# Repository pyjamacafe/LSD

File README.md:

# LSD — Lattice iCE40HX1K-TQ144 USB Breadboard FPGA Core

> [!WARNING]
> **Work in Progress (WIP):** This hardware design is currently a work in progress and has not yet been fabricated or electrically validated on physical silicon. Review the schematic, BOM, and Gerbers carefully before ordering PCBs.

**LSD** (*"Warning: Highly Addictive!"*) is a minimal, breadboardable 2-layer **Lattice iCE40HX1K-TQ144** (1,280 LUTs) FPGA core board designed in **KiCad 10**. It is programmable directly over **USB Micro-B** with **no FTDI bridge chip** by running an open-source RTL USB DFU bootloader (`no2bootloader` / `no2usb`) directly inside the FPGA fabric.

| Top View | Bottom View (Pinout & Logo) |
| :---: | :---: |
|  |  |

---

## Hardware Specifications

* **FPGA:** Lattice `iCE40HX1K-TQ144` (1,280 4-LUTs, 64 kbit EBR, 1× `SB_PLL40_CORE`, 144-pin 0.5 mm TQFP)
* **Form Factor:** `31.2 mm × 64.0 mm` 2-layer FR-4 PCB (1.6 mm) with **`1.5 mm` rounded corners**, filled `B.Cu` ground plane, 45°-mitered routing, and crisp `0.65 mm` non-overlapping top silkscreen references (`0` silk-over-pad)
* **Breadboard Headers:** Two 1×20 2.54 mm through-hole rows (`J3` left, `J4` right) spaced **`27.94 mm` (1.100″ / 11 × 2.54 mm)** apart center-to-center — **36× 3.3V GPIOs**, `+3V3` (top-left), `+5V` VBUS (top-right), and `GND` (bottom-left & bottom-right). Headers are unpopulated by default for user soldering.
* **FTDI-less USB Micro-B (`no2bootloader` ready):** Top-edge horizontal `Molex 47346-0001` (`J1`) → `USBLC6-2SC6` ESD protection (`U5`) → `27 Ω` 1% series damping resistors (`R1`, `R2`) + software-controlled `1.5 kΩ` `D+` pull-up (`R3`, on connector side of `R1`) wired directly to Bank 0 pins `129` (`USB_DN`), `128` (`USB_DP`), and `122` (`USB_PU`).
* **Clock:** `16 MHz` 3.3V CMOS oscillator (`Y1`, Abracon ASE 3.2×2.5 mm) wired to `GBIN6` (Pin `21`), multiplied to an exact `48.000 MHz` via `SB_PLL40_PAD` / `SB_PLL40_CORE` (`DIVR=0`, `DIVF=47`, `DIVQ=4`, `FILTER_RANGE=1`) for Full-Speed USB.
* **SPI Flash:** `W25Q16JVSS` (16 Mbit / 2 MB SOIC-8, `U2`) wired in Master SPI multiboot mode (`Pin 67 SDO → Flash DO`, `Pin 68 SDI → Flash DI`, `Pin 70 SCK`, `Pin 71 SS`) with `10 kΩ` pull-ups on `FLASH_CS_N`, `CRESET_B`, `CDONE`, `~WP`, and `~HOLD`.
* **Push Buttons (Omron `B3U-1000P`):**
  * **`RST` (`SW1`):** Pulls `CRESET_B` (Pin `66`) low to reset and reboot the FPGA from SPI Flash.
  * **`PROG` (`SW2`):** Active-low input on Pin `121` (`PROG_BTN_N`, `10 kΩ` pull-up `R10`). Hold **`PROG`** and tap **`RST`** to keep the FPGA in USB DFU bootloader mode.
* **Power Supply (Sequenced per Lattice `FPGA-TN-02006`):** Independent low-noise LDOs from USB 5V: `AP2112K-1.2` (`U4`, 1.2V Core + RC-filtered `VCCPLL` with isolated local `GNDPLL` return on Pin `35`/`C14`/`C13` — never tied to the main `GND` plane) ramps first, followed by `AP2112K-3.3` (`U3`, 3.3V I/O & Flash, `EN` delayed ~8–36 ms via `R11 = 10 kΩ` / `C19 = 10 µF`), and `1N4148W` drop diode (`D1`) for `VPP_2V5` — guaranteeing `+1V2`/`VCCPLL` (`≥ 0.5 V`) → `+3V3` (`SPI_VCC`) → `VPP_2V5`.
* **One-Time SPI Bootstrap Header (`J2`):** Unpopulated 2×4 2.54 mm header at the bottom edge (`3V3`, `GND`, `CS`, `SCK`, `DI`, `DO`, `RST`, `DN`) for flashing the bootloader once onto a blank SPI Flash.

---

## Verification (KiCad `10.0.3` CLI — Rev `2.5`)

* **Schematic ERC (`kicad-cli sch erc`):** `0` errors, `0` warnings
* **2-Layer PCB DRC (`kicad-cli pcb drc`, saved filled `B.Cu` `GND` zone):** `0` errors, `0` unconnected items, `0` `silk_over_copper` warnings
* **Gerbers (`--check-zones`):** Verified filled `B.Cu` `GND` pour (`G36`), `1.5 mm` rounded `Edge.Cuts`, and 43/43 1:1 BOM/CPL parity

---

## Programming Guide (Direct USB Bootloader)

Because the `iCE40HX1K` has **1,280 LUTs** (no SPRAM), it supports compact pure-Verilog Full-Speed USB bootloaders — such as **`TinyFPGA-Bootloader`** (~950–1,050 LUTs, works out of the box on `HX1K` with `tinyprog`) or a lightweight pure-Verilog **`no2usb`** DFU FSM (note: the full RISC-V `no2bootloader` targets `iCE40UP5K` and exceeds 1,280 LUTs). Both use the exact same hardware (`16 MHz → 48 MHz` PLL, `27 Ω` series `D+`/`D-`, `1.5 kΩ` software `USB_PU`, `W25Q16JVSS` SPI Flash).

### Prerequisites
Install the open-source IceStorm FPGA toolchain + `dfu-util` (e.g., via Homebrew on macOS or [OSS CAD Suite](https://github.com/YosysHQ/oss-cad-suite-build/releases)):
```bash
brew install yosys nextpnr-ice40 icestorm dfu-util
```

### Stage 1: One-Time Bootloader Bring-Up (via `J2`)
A blank `W25Q16JVSS` flash has no bitstream yet, so flash `no2bootloader` **once**:

1. **Build `no2bootloader` for `hx1k` (`tq144`)** using the pinout in [pins.pcf](pins.pcf):
   * `CLK_16M` → Pin `21` (`GBIN6`; 16 MHz → 48.000 MHz exact via `SB_PLL40_PAD`/`SB_PLL40_CORE` with `DIVR=0`, `DIVF=47`, `DIVQ=4`, `FILTER_RANGE=1`)
   * `USB_DP` → Pin `128`, `USB_DN` → Pin `129` (`27 Ω` series), `USB_PU` → Pin `122` (`1.5 kΩ` software pull-up)
   * `PROG_BTN_N` → Pin `121` (active-low, `10 kΩ` pull-up)
   * `FLASH_DO` → `67`, `FLASH_DI` → `68`, `FLASH_SCK` → `70`, `FLASH_CS_N` → `71`
2. **Pack the multiboot image** with `icemulti` (Slot 0 = bootloader, Slot 1 = user bitstream):
   ```bash
   icemulti -v -p0 -a16 -o flash_init.bin boot.bin
   ```
3. **Wire a 3.3V SPI programmer** (Raspberry Pi, RP2040/Pico, FT232H, or 3.3V CH341A) to `J2` (`3V3`, `GND`, `CS`, `SCK`, `DI`, `DO`) and hold **`RST` (`CRESET_B`) LOW** to tri-state the FPGA SPI pins.
4. **Flash `flash_init.bin` to `W25Q16JVSS` at offset `0x000000`:**
   ```bash
   flashrom -p <your_3v3_programmer> -w flash_init.bin
   ```
5. **Release `RST` and disconnect `J2`.** All future programming happens over USB Micro-B.

### Stage 2: Everyday Programming Over USB Micro-B
1. **Synthesize and pack your Verilog design:**
   ```bash
   yosys -p "synth_ice40 -top top -json build.json" top.v
   nextpnr-ice40 --hx1k --package tq144 --pcf pins.pcf --json build.json --asc build.asc
   icepack build.asc build.bin
   ```
2. **Enter USB DFU mode:** Plug in USB Micro-B, **hold `PROG`**, **tap `RST`**, then release `PROG`. Verify with `dfu-util -l`.
3. **Flash over USB:**
   ```bash
   dfu-util -a 0 -D build.bin -R
   ```
   The `-R` flag triggers `SB_WARMBOOT` to immediately reboot into your design. Tap **`RST`** anytime to reboot.

---

## Interactive 3D Viewer & Project Files

To inspect the photorealistic PBR 3D board in your browser:
```bash
python3 -m http.server 8000
# Open http://localhost:8000/viewer.html
```

| Path | Description |
| :--- | :--- |
| `ice40hx1k_usb_core.kicad_pro` | KiCad 10 project & 2-layer design rules |
| `ice40hx1k_usb_core.kicad_sch` | Complete schematic (`0` ERC violations) |
| `ice40hx1k_usb_core.kicad_pcb` | Routed `31.2 × 64.0 mm` 2-layer PCB (`0` DRC errors, `0` unconnected) |
| `pins.pcf` | IceStorm / `nextpnr-ice40` pin constraint file matching back silkscreen |
| `fab/gerbers/` | Fabrication-ready 2-layer Gerber X2 + Excellon `.drl` + drill map |
| `fab/bom.csv` | Bill of Materials |
| `fab/lioncircuits/` | LionCircuits-formatted Gerber `.zip`, BOM `.xlsx`/`.csv`, and CPL `.xlsx`/`.csv` |
| `renders/ice40hx1k_usb_core.glb` | Full-detail PBR 3D model (WebGL / Three.js / `<model-viewer>`) |
| `renders/ice40hx1k_usb_core.step` | Mechanical CAD 3D model (Fusion 360 / FreeCAD / SolidWorks) |
| `renders/schematic.pdf` | Printable schematic PDF |
| `renders/logo.{svg,png,jpg}` | LSD square stamp-heart logo assets |
| `viewer.html` | Interactive `<model-viewer>` 3D PCB viewer |

---

## License

Released under the [MIT License](LICENSE).

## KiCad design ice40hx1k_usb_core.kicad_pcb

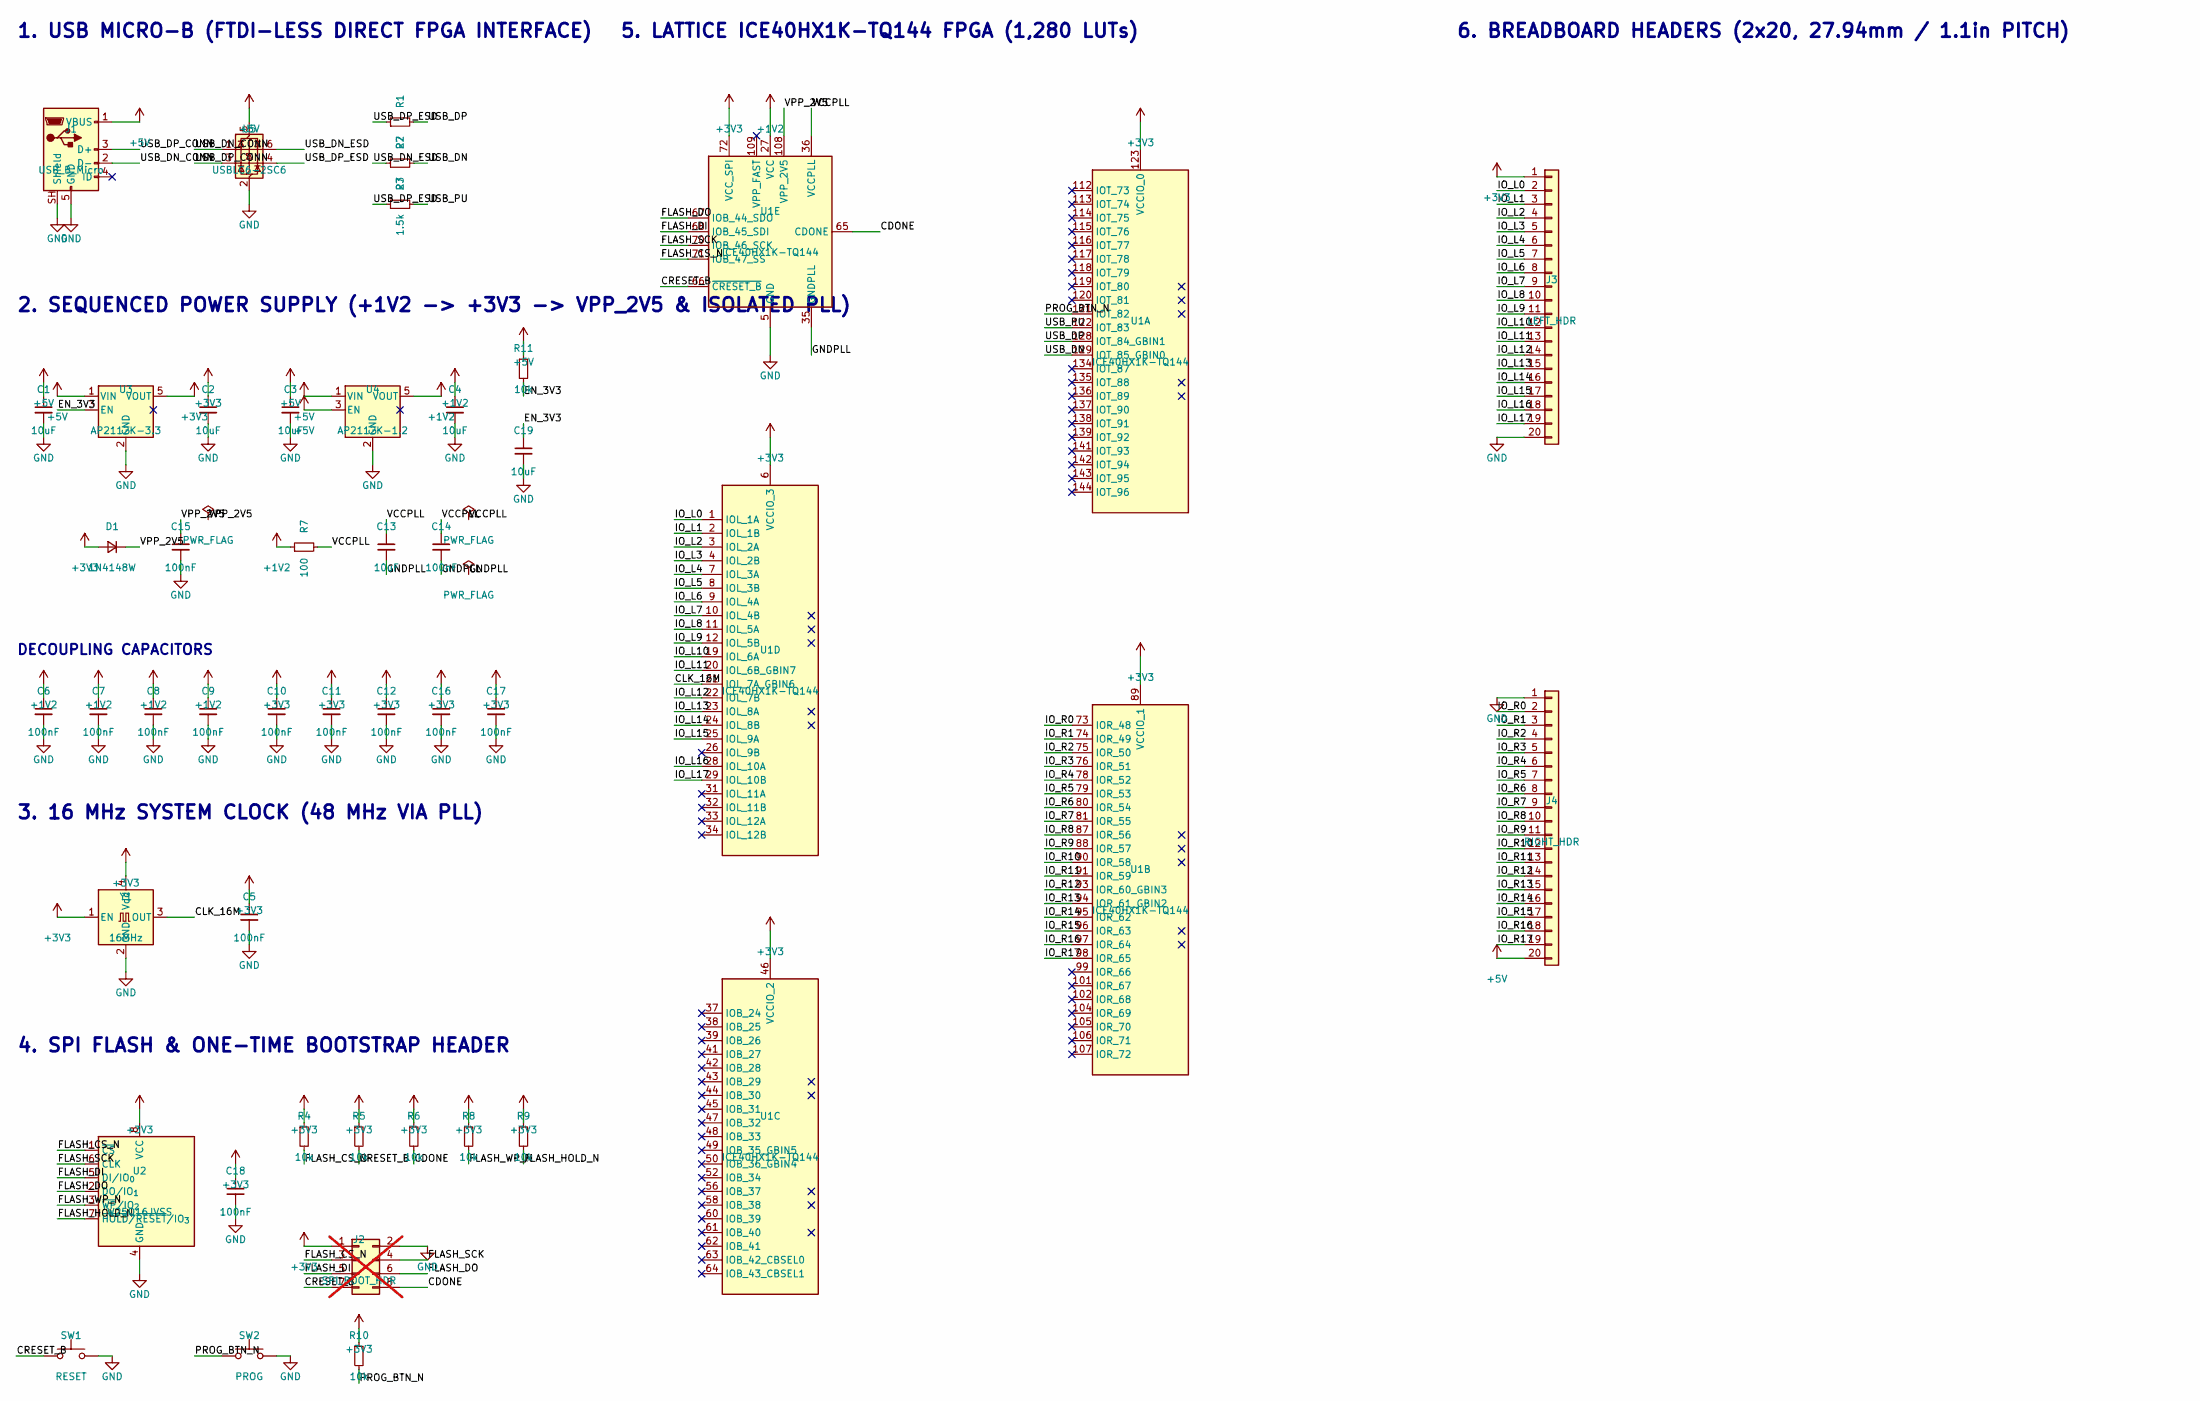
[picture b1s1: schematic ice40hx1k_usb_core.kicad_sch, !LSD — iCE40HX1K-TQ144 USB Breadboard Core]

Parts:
C1, C2, C3, C4, C13, C19: 10uF; C_0603_1608Metric
C5, C6, C7, C8, C9, C10, C11, C12, C14, C15, C16, C17, C18: 100nF; C_0603_1608Metric
D1: 1N4148W; D_SOD-123
J1: USB_B_Micro; USB_Micro-B_Molex_47346-0001
J2: SPI_BOOT_HDR; PinHeader_2x04_P2.54mm_Vertical; not fitted
J3: LEFT_HDR; PinHeader_1x20_P2.54mm_Vertical
J4: RIGHT_HDR; PinHeader_1x20_P2.54mm_Vertical
R1, R2: 27; R_0603_1608Metric
R3: 1.5k; R_0603_1608Metric
R4, R5, R6, R8, R9, R10, R11: 10k; R_0603_1608Metric
R7: 100; R_0603_1608Metric
SW1: RESET; SW_SPST_B3U-1000P
SW2: PROG; SW_SPST_B3U-1000P
U1: ICE40HX1K-TQ144; TQFP-144_20x20mm_P0.5mm
U2: W25Q16JVSS; SOIC-8_5.3x5.3mm_P1.27mm
U3: AP2112K-3.3; SOT-23-5
U4: AP2112K-1.2; SOT-23-5
U5: USBLC6-2SC6; SOT-23-6
Y1: 16MHz; Oscillator_SMD_Abracon_ASE-4Pin_3.2x2.5mm

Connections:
+1V2: C4.1, C6.1, C7.1, C8.1, C9.1, R7.1, U1.27 (VCC), U1.51 (VCC), U1.92 (VCC), U1.111 (VCC), U4.5 (VOUT)
+3V3: C2.1, C5.1, C10.1, C11.1, C12.1, C16.1, C17.1, C18.1, D1.2 (A), J2.1, J3.1, R4.1, R5.1, R6.1, R8.1, R9.1, R10.1, U1.6 (VCCIO_3), U1.30 (VCCIO_3), U1.46 (VCCIO_2), U1.57 (VCCIO_2), U1.72 (VCC_SPI), U1.89 (VCCIO_1), U1.100 (VCCIO_1), U1.123 (VCCIO_0), U1.133 (VCCIO_0), U2.8 (VCC), U3.5 (VOUT), Y1.1 (EN), Y1.4 (Vdd)
+5V: C1.1, C3.1, J1.1 (VBUS), J4.20, R11.1, U3.1 (VIN), U4.1 (VIN), U4.3 (EN), U5.5 (VBUS)
CDONE: J2.8, R6.2, U1.65 (CDONE)
CLK_16M: U1.21 (IOL_7A_GBIN6), Y1.3 (OUT)
CRESET_B: J2.7, R5.2, SW1.1, U1.66 (~CRESET_B)
EN_3V3: C19.1, R11.2, U3.3 (EN)
FLASH_CS_N: J2.3, R4.2, U1.71 (IOB_47_SS), U2.1 (~CS)
FLASH_DI: J2.5, U1.68 (IOB_45_SDI), U2.5 (DI/IO_{0})
FLASH_DO: J2.6, U1.67 (IOB_44_SDO), U2.2 (DO/IO_{1})
FLASH_HOLD_N: R9.2, U2.7 (~HOLD/~RESET/IO_{3})
FLASH_SCK: J2.4, U1.70 (IOB_46_SCK), U2.6 (CLK)
FLASH_WP_N: R8.2, U2.3 (~WP/IO_{2})
GND: C1.2, C2.2, C3.2, C4.2, C5.2, C6.2, C7.2, C8.2, C9.2, C10.2, C11.2, C12.2, C15.2, C16.2, C17.2, C18.2, C19.2, J1.5 (GND), J1.SH (Shield), J2.2, J3.20, J4.1, SW1.2, SW2.2, U1.5 (GND), U1.13 (GND), U1.14 (GND), U1.59 (GND), U1.69 (GND), U1.86 (GND), U1.103 (GND), U1.132 (GND), U1.140 (GND), U2.4 (GND), U3.2 (GND), U4.2 (GND), U5.2 (GND), Y1.2 (GND)
GNDPLL: C13.2, C14.2, U1.35 (GNDPLL)
IO_L0: J3.2, U1.1 (IOL_1A)
IO_L1: J3.3, U1.2 (IOL_1B)
IO_L2: J3.4, U1.3 (IOL_2A)
IO_L3: J3.5, U1.4 (IOL_2B)
IO_L4: J3.6, U1.7 (IOL_3A)
IO_L5: J3.7, U1.8 (IOL_3B)
IO_L6: J3.8, U1.9 (IOL_4A)
IO_L7: J3.9, U1.10 (IOL_4B)
IO_L8: J3.10, U1.11 (IOL_5A)
IO_L9: J3.11, U1.12 (IOL_5B)
IO_L10: J3.12, U1.19 (IOL_6A)
IO_L11: J3.13, U1.20 (IOL_6B_GBIN7)
IO_L12: J3.14, U1.22 (IOL_7B)
IO_L13: J3.15, U1.23 (IOL_8A)
IO_L14: J3.16, U1.24 (IOL_8B)
IO_L15: J3.17, U1.25 (IOL_9A)
IO_L16: J3.18, U1.28 (IOL_10A)
IO_L17: J3.19, U1.29 (IOL_10B)
IO_R0: J4.2, U1.73 (IOR_48)
IO_R1: J4.3, U1.74 (IOR_49)
IO_R2: J4.4, U1.75 (IOR_50)
IO_R3: J4.5, U1.76 (IOR_51)
IO_R4: J4.6, U1.78 (IOR_52)
IO_R5: J4.7, U1.79 (IOR_53)
IO_R6: J4.8, U1.80 (IOR_54)
IO_R7: J4.9, U1.81 (IOR_55)
IO_R8: J4.10, U1.87 (IOR_56)
IO_R9: J4.11, U1.88 (IOR_57)
IO_R10: J4.12, U1.90 (IOR_58)
IO_R11: J4.13, U1.91 (IOR_59)
IO_R12: J4.14, U1.93 (IOR_60_GBIN3)
IO_R13: J4.15, U1.94 (IOR_61_GBIN2)
IO_R14: J4.16, U1.95 (IOR_62)
IO_R15: J4.17, U1.96 (IOR_63)
IO_R16: J4.18, U1.97 (IOR_64)
IO_R17: J4.19, U1.98 (IOR_65)
PROG_BTN_N: R10.2, SW2.1, U1.121 (IOT_82)
USB_DN: R2.2, U1.129 (IOT_85_GBIN0)
USB_DN_CONN: J1.2 (D-), U5.1 (I/O1)
USB_DN_ESD: R2.1, U5.6 (I/O1)
USB_DP: R1.2, U1.128 (IOT_84_GBIN1)
USB_DP_CONN: J1.3 (D+), U5.3 (I/O2)
USB_DP_ESD: R1.1, R3.1, U5.4 (I/O2)
USB_PU: R3.2, U1.122 (IOT_83)
VCCPLL: C13.1, C14.1, R7.2, U1.36 (VCCPLL)
VPP_2V5: C15.1, D1.1 (K), U1.108 (VPP_2V5)

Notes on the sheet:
1. USB MICRO-B (FTDI-LESS DIRECT FPGA INTERFACE)
2. SEQUENCED POWER SUPPLY (+1V2 -> +3V3 -> VPP_2V5 & ISOLATED PLL)
DECOUPLING CAPACITORS
3. 16 MHz SYSTEM CLOCK (48 MHz VIA PLL)
4. SPI FLASH & ONE-TIME BOOTSTRAP HEADER
5. LATTICE ICE40HX1K-TQ144 FPGA (1,280 LUTs)
6. BREADBOARD HEADERS (2x20, 27.94mm / 1.1in PITCH)

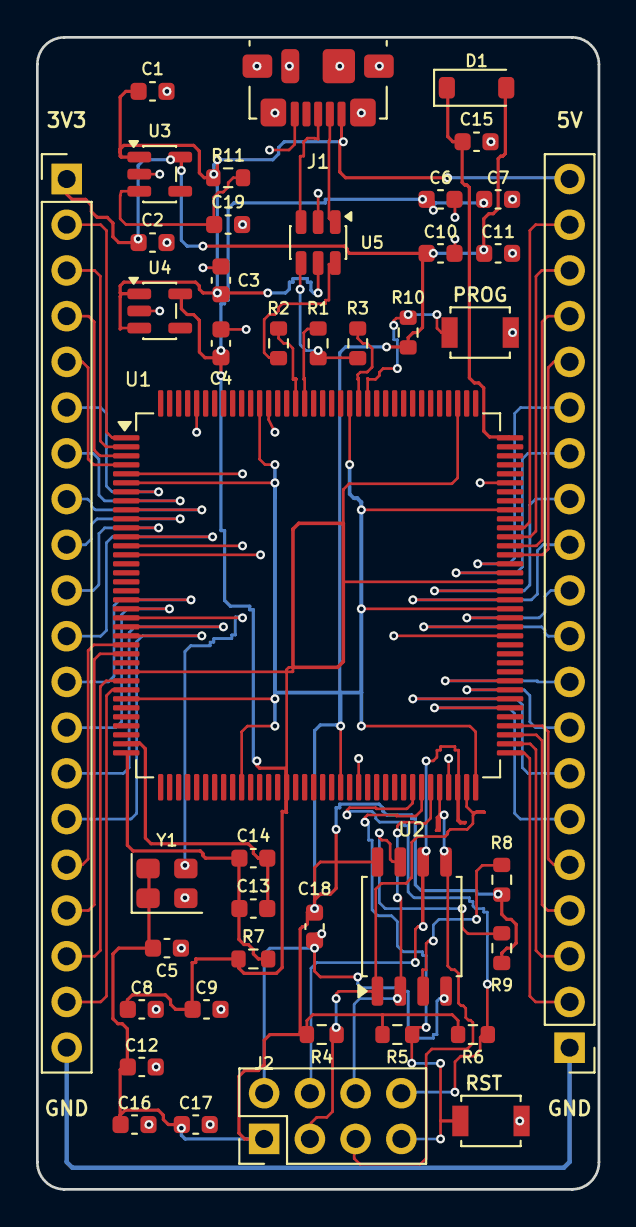
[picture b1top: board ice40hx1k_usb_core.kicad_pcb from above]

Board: 2 copper layers, 31.2 x 64.0 mm, 43 parts (0 on the bottom side), 61 nets.

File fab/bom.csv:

"Refs","Value","Footprint","Qty","DNP"
"C1","10uF","Capacitor_SMD:C_0603_1608Metric","1",""
"C2","10uF","Capacitor_SMD:C_0603_1608Metric","1",""
"C3","10uF","Capacitor_SMD:C_0603_1608Metric","1",""
"C4","10uF","Capacitor_SMD:C_0603_1608Metric","1",""
"C5","100nF","Capacitor_SMD:C_0603_1608Metric","1",""
"C6","100nF","Capacitor_SMD:C_0603_1608Metric","1",""
"C7","100nF","Capacitor_SMD:C_0603_1608Metric","1",""
"C8","100nF","Capacitor_SMD:C_0603_1608Metric","1",""
"C9","100nF","Capacitor_SMD:C_0603_1608Metric","1",""
"C10","100nF","Capacitor_SMD:C_0603_1608Metric","1",""
"C11","100nF","Capacitor_SMD:C_0603_1608Metric","1",""
"C12","100nF","Capacitor_SMD:C_0603_1608Metric","1",""
"C13","10uF","Capacitor_SMD:C_0603_1608Metric","1",""
"C14","100nF","Capacitor_SMD:C_0603_1608Metric","1",""
"C15","100nF","Capacitor_SMD:C_0603_1608Metric","1",""
"C16","100nF","Capacitor_SMD:C_0603_1608Metric","1",""
"C17","100nF","Capacitor_SMD:C_0603_1608Metric","1",""
"C18","100nF","Capacitor_SMD:C_0603_1608Metric","1",""
"C19","10uF","Capacitor_SMD:C_0603_1608Metric","1",""
"D1","1N4148W","Diode_SMD:D_SOD-123","1",""
"J1","USB_B_Micro","Connector_USB:USB_Micro-B_Molex_47346-0001","1",""
"J2","SPI_BOOT_HDR","Connector_PinHeader_2.54mm:PinHeader_2x04_P2.54mm_Vertical","1","DNP"
"J3","LEFT_HDR","Connector_PinHeader_2.54mm:PinHeader_1x20_P2.54mm_Vertical","1",""
"J4","RIGHT_HDR","Connector_PinHeader_2.54mm:PinHeader_1x20_P2.54mm_Vertical","1",""
"R1","27","Resistor_SMD:R_0603_1608Metric","1",""
"R2","27","Resistor_SMD:R_0603_1608Metric","1",""
"R3","1.5k","Resistor_SMD:R_0603_1608Metric","1",""
"R4","10k","Resistor_SMD:R_0603_1608Metric","1",""
"R5","10k","Resistor_SMD:R_0603_1608Metric","1",""
"R6","10k","Resistor_SMD:R_0603_1608Metric","1",""
"R7","100","Resistor_SMD:R_0603_1608Metric","1",""
"R8","10k","Resistor_SMD:R_0603_1608Metric","1",""
"R9","10k","Resistor_SMD:R_0603_1608Metric","1",""
"R10","10k","Resistor_SMD:R_0603_1608Metric","1",""
"R11","10k","Resistor_SMD:R_0603_1608Metric","1",""
"SW1","RESET","Button_Switch_SMD:SW_SPST_B3U-1000P","1",""
"SW2","PROG","Button_Switch_SMD:SW_SPST_B3U-1000P","1",""
"U1","ICE40HX1K-TQ144","Package_QFP:TQFP-144_20x20mm_P0.5mm","1",""
"U2","W25Q16JVSS","Package_SO:SOIC-8_5.3x5.3mm_P1.27mm","1",""
"U3","AP2112K-3.3","Package_TO_SOT_SMD:SOT-23-5","1",""
"U4","AP2112K-1.2","Package_TO_SOT_SMD:SOT-23-5","1",""
"U5","USBLC6-2SC6","Package_TO_SOT_SMD:SOT-23-6","1",""
"Y1","16MHz","Oscillator:Oscillator_SMD_Abracon_ASE-4Pin_3.2x2.5mm","1",""

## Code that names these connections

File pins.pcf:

# LSD — Lattice iCE40HX1K-TQ144 USB Breadboard Core (Pico-Style 1.1" Pitch) — Pin Constraints (.pcf)
# Matches the B.SilkS pin labels printed on the back of the PCB (e.g. L0/P1 .. R17/P98).
# Compatible with Yosys / nextpnr-ice40 / IceStorm / no2bootloader (no2usb DFU).

# ---------------------------------------------------------------------------
# System Clock & Direct FTDI-less USB Full-Speed Interface (no2bootloader)
# ---------------------------------------------------------------------------
# 16 MHz -> 48.000 MHz exact via SB_PLL40_PAD / SB_PLL40_CORE:
#   DIVR=4'b0000 (0), DIVF=7'b0101111 (47), DIVQ=3'b100 (4), FILTER_RANGE=3'b001 (1)
set_io CLK_16M 21   # 16 MHz Oscillator (GBIN6 -> SB_PLL40_PAD/CORE -> 48 MHz USB)
set_io USB_DN 129   # USB Micro-B D- (via 27R + USBLC6-2SC6)
set_io USB_DP 128   # USB Micro-B D+ (via 27R + USBLC6-2SC6)
set_io USB_PU 122   # USB D+ 1.5k software pull-up control (active-high attach / Hi-Z detach)
set_io PROG_BTN_N 121  # SW2 (PROG) active-low push button (10k pull-up; hold + tap RST for USB DFU prog mode)

# ---------------------------------------------------------------------------
# External SPI Flash (W25Q16JVSS) — Master SPI Boot & Bootloader Flash Access
# ---------------------------------------------------------------------------
set_io FLASH_DO   67  # Flash DO / IO1 (Master MISO)
set_io FLASH_DI   68  # Flash DI / IO0 (Master MOSI)
set_io FLASH_SCK  70  # Flash CLK
set_io FLASH_CS_N 71  # Flash ~CS (10k pull-up for Master SPI boot)

# ---------------------------------------------------------------------------
# Left 1x20 Breadboard Header J3 (Top -> Bottom: Pin 1 = 3V3, Pin 20 = GND)
# ---------------------------------------------------------------------------
set_io L0  1    # J3 Pin 2  | PCB Silk: L0/P1   (Bank 3, IOL_1A)
set_io L1  2    # J3 Pin 3  | PCB Silk: L1/P2   (Bank 3, IOL_1B)
set_io L2  3    # J3 Pin 4  | PCB Silk: L2/P3   (Bank 3, IOL_2A)
set_io L3  4    # J3 Pin 5  | PCB Silk: L3/P4   (Bank 3, IOL_2B)
set_io L4  7    # J3 Pin 6  | PCB Silk: L4/P7   (Bank 3, IOL_3A)
set_io L5  8    # J3 Pin 7  | PCB Silk: L5/P8   (Bank 3, IOL_3B)
set_io L6  9    # J3 Pin 8  | PCB Silk: L6/P9   (Bank 3, IOL_4A)
set_io L7  10   # J3 Pin 9  | PCB Silk: L7/P10  (Bank 3, IOL_4B)
set_io L8  11   # J3 Pin 10 | PCB Silk: L8/P11  (Bank 3, IOL_5A)
set_io L9  12   # J3 Pin 11 | PCB Silk: L9/P12  (Bank 3, IOL_5B)
set_io L10 19   # J3 Pin 12 | PCB Silk: L10/P19 (Bank 3, IOL_6A)
set_io L11 20   # J3 Pin 13 | PCB Silk: L11/P20 (Bank 3, IOL_6B_GBIN7)
set_io L12 22   # J3 Pin 14 | PCB Silk: L12/P22 (Bank 3, IOL_7B)
set_io L13 23   # J3 Pin 15 | PCB Silk: L13/P23 (Bank 3, IOL_8A)
set_io L14 24   # J3 Pin 16 | PCB Silk: L14/P24 (Bank 3, IOL_8B)
set_io L15 25   # J3 Pin 17 | PCB Silk: L15/P25 (Bank 3, IOL_9A)
set_io L16 28   # J3 Pin 18 | PCB Silk: L16/P28 (Bank 3, IOL_10A)
set_io L17 29   # J3 Pin 19 | PCB Silk: L17/P29 (Bank 3, IOL_10B)

# ---------------------------------------------------------------------------
# Right 1x20 Breadboard Header J4 (Top -> Bottom: Pin 20 = 5V, Pin 1 = GND)
# ---------------------------------------------------------------------------
set_io R17 98   # J4 Pin 19 | PCB Silk: R17/P98 (Bank 1, IOR_65)
set_io R16 97   # J4 Pin 18 | PCB Silk: R16/P97 (Bank 1, IOR_64)
set_io R15 96   # J4 Pin 17 | PCB Silk: R15/P96 (Bank 1, IOR_63)
set_io R14 95   # J4 Pin 16 | PCB Silk: R14/P95 (Bank 1, IOR_62)
set_io R13 94   # J4 Pin 15 | PCB Silk: R13/P94 (Bank 1, IOR_61_GBIN2)
set_io R12 93   # J4 Pin 14 | PCB Silk: R12/P93 (Bank 1, IOR_60_GBIN3)
set_io R11 91   # J4 Pin 13 | PCB Silk: R11/P91 (Bank 1, IOR_59)
set_io R10 90   # J4 Pin 12 | PCB Silk: R10/P90 (Bank 1, IOR_58)
set_io R9  88   # J4 Pin 11 | PCB Silk: R9/P88  (Bank 1, IOR_57)
set_io R8  87   # J4 Pin 10 | PCB Silk: R8/P87  (Bank 1, IOR_56)
set_io R7  81   # J4 Pin 9  | PCB Silk: R7/P81  (Bank 1, IOR_55)
set_io R6  80   # J4 Pin 8  | PCB Silk: R6/P80  (Bank 1, IOR_54)
set_io R5  79   # J4 Pin 7  | PCB Silk: R5/P79  (Bank 1, IOR_53)
set_io R4  78   # J4 Pin 6  | PCB Silk: R4/P78  (Bank 1, IOR_52)
set_io R3  76   # J4 Pin 5  | PCB Silk: R3/P76  (Bank 1, IOR_51)
set_io R2  75   # J4 Pin 4  | PCB Silk: R2/P75  (Bank 1, IOR_50)
set_io R1  74   # J4 Pin 3  | PCB Silk: R1/P74  (Bank 1, IOR_49)
set_io R0  73   # J4 Pin 2  | PCB Silk: R0/P73  (Bank 1, IOR_48)
